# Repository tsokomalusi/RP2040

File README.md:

# Custom PCB Design Raspberry Pi Pico (RP2040)
I designed a custom PCB based on the RP2040 microcontroller using KiCad 9.0,
following the official RP2040 hardware design guidelines.This version includes
several enhancements to improve usability and protection:
- ESD protection on the USB interface
- SWD header for debugging
- Dedicated Boot and Reset push-buttons

## Schematic

## PCB Layout

## 3D Model

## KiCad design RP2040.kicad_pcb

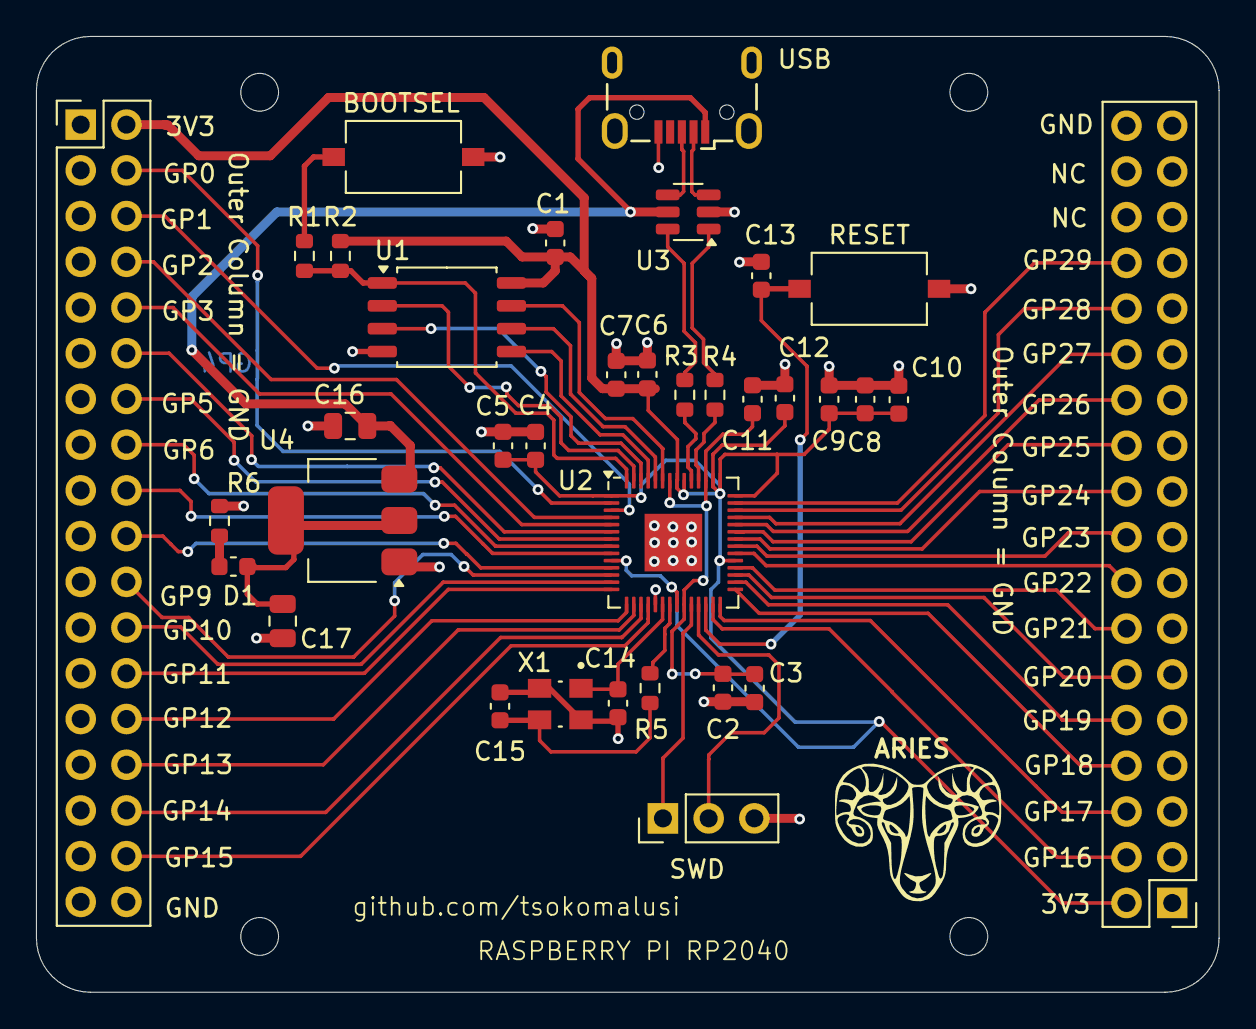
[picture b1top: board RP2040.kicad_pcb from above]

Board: 4 copper layers, 65.7 x 53.1 mm, 39 parts (0 on the bottom side), 55 nets.

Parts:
BOOTSEL: BOOTSEL; SW_Tactile_SPST_NO_Straight_CK_PTS636Sx25SMTRLFS
C1, C2, C3, C4, C5, C6, C7, C8, C9, C10, C13: 100n; C_0603_1608Metric
C11, C12: 1u; C_0603_1608Metric
C14, C15: 10p; C_0603_1608Metric
C16, C17: 10u; C_0805_2012Metric
D1: GREEN; C_0603_1608Metric
H1, H2, H3, H4: MountingHole; MountingHole_2.1mm
J1, J2: Conn_02x18_Odd_Even; PinHeader_2x18_P2.54mm_Vertical
R1, R5: 1K; R_0603_1608Metric
R2: DNF; R_0603_1608Metric
R3, R4: 27R; R_0603_1608Metric
R6: 1K5; R_0603_1608Metric
RESET: RESET; SW_Tactile_SPST_NO_Straight_CK_PTS636Sx25SMTRLFS
SWD: Conn_01x03; PinHeader_1x03_P2.54mm_Vertical
U1: W25Q128JVS; SOIC-8_5.3x5.3mm_P1.27mm
U2: RP2040; QFN-56-1EP_7x7mm_P0.4mm_EP3.2x3.2mm
U3: USBLC6-2SC6; SOT-23-6
U4: AMS1117-3.3; SOT-223-3_TabPin2
USB: USB_B_Micro; USB_Micro-B_Wuerth_629105150521
X1: 12MHz; XTAL_ABM8-272-T3

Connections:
+1V1: C2.1, C3.1, C11.1, U2.23 (DVDD), U2.45 (VREG_VOUT), U2.50 (DVDD)
+3V3: C1.1, C4.1, C5.1, C6.1, C7.1, C8.1, C9.1, C10.1, C12.1, J1.2, J2.2, R2.1, U1.8 (VCC), U2.1 (IOVDD), U2.10 (IOVDD), U2.22 (IOVDD), U2.33 (IOVDD), U2.42 (IOVDD), U2.43 (ADC_AVDD), U2.44 (VREG_IN), U2.48 (USB_VDD), U2.49 (IOVDD)
/USB_D+: R3.2, U2.47 (USB_DP)
/USB_D-: R4.2, U2.46 (USB_DM)
/U_D+: R3.1, U3.6 (I/O1)
/U_D-: R4.1, U3.1 (I/O1)
GND: BOOTSEL.1 (A), C1.2, C2.2, C3.2, C4.2, C5.2, C6.2, C7.2, C8.2, C9.2, C10.2, C11.2, C12.2, C13.1, C14.1, C15.1, C16.2, C17.2, J1.1, J1.3, J1.5, J1.7, J1.9, J1.11, J1.13, J1.15, J1.17, J1.19, J1.21, J1.23, J1.25, J1.27, J1.29, J1.31, J1.33, J1.35, J1.36, J2.1, J2.3, J2.5, J2.7, J2.9, J2.11, J2.13, J2.15, J2.17, J2.19, J2.21, J2.23, J2.25, J2.27, J2.29, J2.31, J2.33, J2.35, J2.36, R6.2, RESET.1 (A), SWD.3, U1.4 (GND), U2.19 (TESTEN), U2.57 (GND), U3.2 (GND), U4.1 (GND), USB.5 (GND), USB.6 (Shield), X1.2, X1.4
GPIO0: J1.4, U2.2 (GPIO0)
GPIO1: J1.6, U2.3 (GPIO1)
GPIO2: J1.8, U2.4 (GPIO2)
GPIO3: J1.10, U2.5 (GPIO3)
GPIO4: J1.12, U2.6 (GPIO4)
GPIO5: J1.14, U2.7 (GPIO5)
GPIO6: J1.16, U2.8 (GPIO6)
GPIO7: J1.18, U2.9 (GPIO7)
GPIO8: J1.20, U2.11 (GPIO8)
GPIO9: J1.22, U2.12 (GPIO9)
GPIO10: J1.24, U2.13 (GPIO10)
GPIO11: J1.26, U2.14 (GPIO11)
GPIO12: J1.28, U2.15 (GPIO12)
GPIO13: J1.30, U2.16 (GPIO13)
GPIO14: J1.32, U2.17 (GPIO14)
GPIO15: J1.34, U2.18 (GPIO15)
GPIO16: J2.4, U2.27 (GPIO16)
GPIO17: J2.6, U2.28 (GPIO17)
GPIO18: J2.8, U2.29 (GPIO18)
GPIO19: J2.10, U2.30 (GPIO19)
GPIO20: J2.12, U2.31 (GPIO20)
GPIO21: J2.14, U2.32 (GPIO21)
GPIO22: J2.16, U2.34 (GPIO22)
GPIO23: J2.18, U2.35 (GPIO23)
GPIO24: J2.20, U2.36 (GPIO24)
GPIO25: J2.22, U2.37 (GPIO25)
GPIO26_ADC0: J2.24, U2.38 (GPIO26_ADC0)
GPIO27_ADC1: J2.26, U2.39 (GPIO27_ADC1)
GPIO28_ADC2: J2.28, U2.40 (GPIO28_ADC2)
GPIO29_ADC3: J2.30, U2.41 (GPIO29_ADC3)
unnamed: C15.2, R5.1, X1.3
unnamed: C17.1, D1.2 (A), U4.2 (VO)
unnamed: D1.1 (K), R6.1
unnamed: BOOTSEL.2 (B), R1.1
unnamed: C13.2, RESET.2 (B), U2.26 (RUN)
QSPI_SCLK: U1.6 (CLK), U2.52 (QSPI_SCLK)
QSPI_SD0: U1.5 (DI/IO_{0}), U2.53 (QSPI_SD0)
QSPI_SD1: U1.2 (DO/IO_{1}), U2.55 (QSPI_SD1)
QSPI_SD2: U1.3 (~WP/IO_{2}), U2.54 (QSPI_SD2)
QSPI_SD3: U1.7 (~HOLD/~RESET/IO_{3}), U2.51 (QSPI_SD3)
QSPI_SS: R1.2, R2.2, U1.1 (~CS), U2.56 (QSPI_SS)
SWCLK: SWD.1, U2.24 (SWCLK)
SWD: SWD.2, U2.25 (SWD)
USB_CONN_D+: U3.4 (I/O2), USB.3 (D+)
USB_CONN_D-: U3.3 (I/O2), USB.2 (D-)
VBUS: C16.1, U3.5 (VBUS), U4.3 (VI), USB.1 (VBUS)
XIN: C14.2, U2.20 (XIN), X1.1
XOUT: R5.2, U2.21 (XOUT)

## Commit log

2025-07-15 uploading all files
2025-07-16 adding the schematic
